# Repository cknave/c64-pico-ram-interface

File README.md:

# Commodore 64 to Raspberry Pi Pico RAM interface

This project exposes a 16 KiB window of a Raspberry Pi Pico's RAM to a Commodore 64 via the
expansion port. It includes a hardware design and software for the Pico C++ SDK.

<table style="border-collapse: collapse"><tr>
<td><figure>
<figcaption>PCB image</figcaption></figure></td>
<td><figure>
<figcaption>Demo video</figcaption></figure>
</tr></table>

## The hardware

**[Schematic PDF](./docs/schematic.pdf)**

Schematic, PCB, and project files are in KiCad 6 format.

5V power from the expansion port is used to power the Pico. As suggested in the Pico datasheet,
a Schottky diode allows the Pico to be connected to powered USB at the same time. 

8-bit buffers bring the 5V logic levels on the address and data bus down to 3.3V to protect
the Pico's GPIO pins. This means that when the C64 reads from the Pico, it's putting a 3.3V
signal on the data bus.  At TTL logic levels, this should be fine.

A switch allows you to toggle between an 8K ROM and a 16K ROM by pulling the /GAME line low.
This loses half the address space, but lets you boot into BASIC.

The tolerances on the PCB design are compatible with [JLCPCB](https://jlcpcb.com/). I ordered
my prototypes from them with ENIG surface finish and gold fingers on a 1.6mm thick board.  You
can get them made much cheaper with HASL, but it will eventually scrape off as you reinsert
the board.

## The firmware

Given a 16 KiB-aligned base address on the Pico's address space, four PIO state machines and
two DMA channels handle reading addresses from the C64 address bus and writing the requested
data to the C64 data bus. The CPU is not needed once this is configured.

To allow the C64 to communicate with the Pico, a 256 byte **command area** is reserved that
will put that byte onto the RX FIFO for the CPU to consume.  The CPU can put any value onto
the TX FIFO to signal that it is ready for more commands.

Between the GPIO pins and the RAM, there are five logical components:

- **address_decoder PIO state machine:** monitors the /ROML and /ROMH lines for reads,
  checks if the address is for the special **command area**, and wakes up either the **read**
  or **command** state machines as needed.  Two copies of this state machine run at the same
  time, monitoring /ROML and /ROMH.
- **read PIO state machine:** reads the address lines, sends the address to DMA, and writes
  the returned data to the data bus
- **command PIO state machine:** reads the low 8 bits of the address, and copies it to the
  RX FIFO for the CPU to handle.  It writes the STATUS register back to the data bus, indicating
  if the CPU is busy or not. The CPU can indicate its readiness by writing any value to the TX FIFO.

  The special value `00` will not be sent to the CPU at all, allowing the C64 to poll the status
  register until the Pico is finished processing a command.
- **DMA channel 1**: write the incoming address to the configuration of DMA channel 2, triggering
  a read
- **DMA channel 2**: copy a byte at the requested RAM address to the read PIO state machine

It's a Rube Goldberg machine, but the Pico's PIO controllers and DMA can do this in well under
the time required by the C64's CPU.

## Further improvements

### Could this work as a 16K ROM and IO ports?

Maybe, but this design is already using all the GPIO pins on the Pico.  Even if you replace
the "input enable" pin (you can probably get away without it), you'll also need to monitor
PHI2.  In my experience, the IO lines are glitchy and you need to make sure that you're actually
in the right part of the clock cycle to use them.

You could try using a shift register to free up a bunch of pins, but you'll waste a lot of
PIO clock cycles shifting all the bits through it.  It might be fast enough to only shift a
couple of bits.

### Could I use all 44 KiB of the available address space?

I think you're definitely in shift register territory at this point, and good luck trying to
decode more than a couple of address prefixes in PIO.  If you actually do this, please contact
me because I want to see it!

## Legal

Distribute under the terms of the BSD 3-clause license.

The [KiCad-RP-Pico footprint](https://github.com/ncarandini/KiCad-RP-Pico) is by
Nicolò Carandini.

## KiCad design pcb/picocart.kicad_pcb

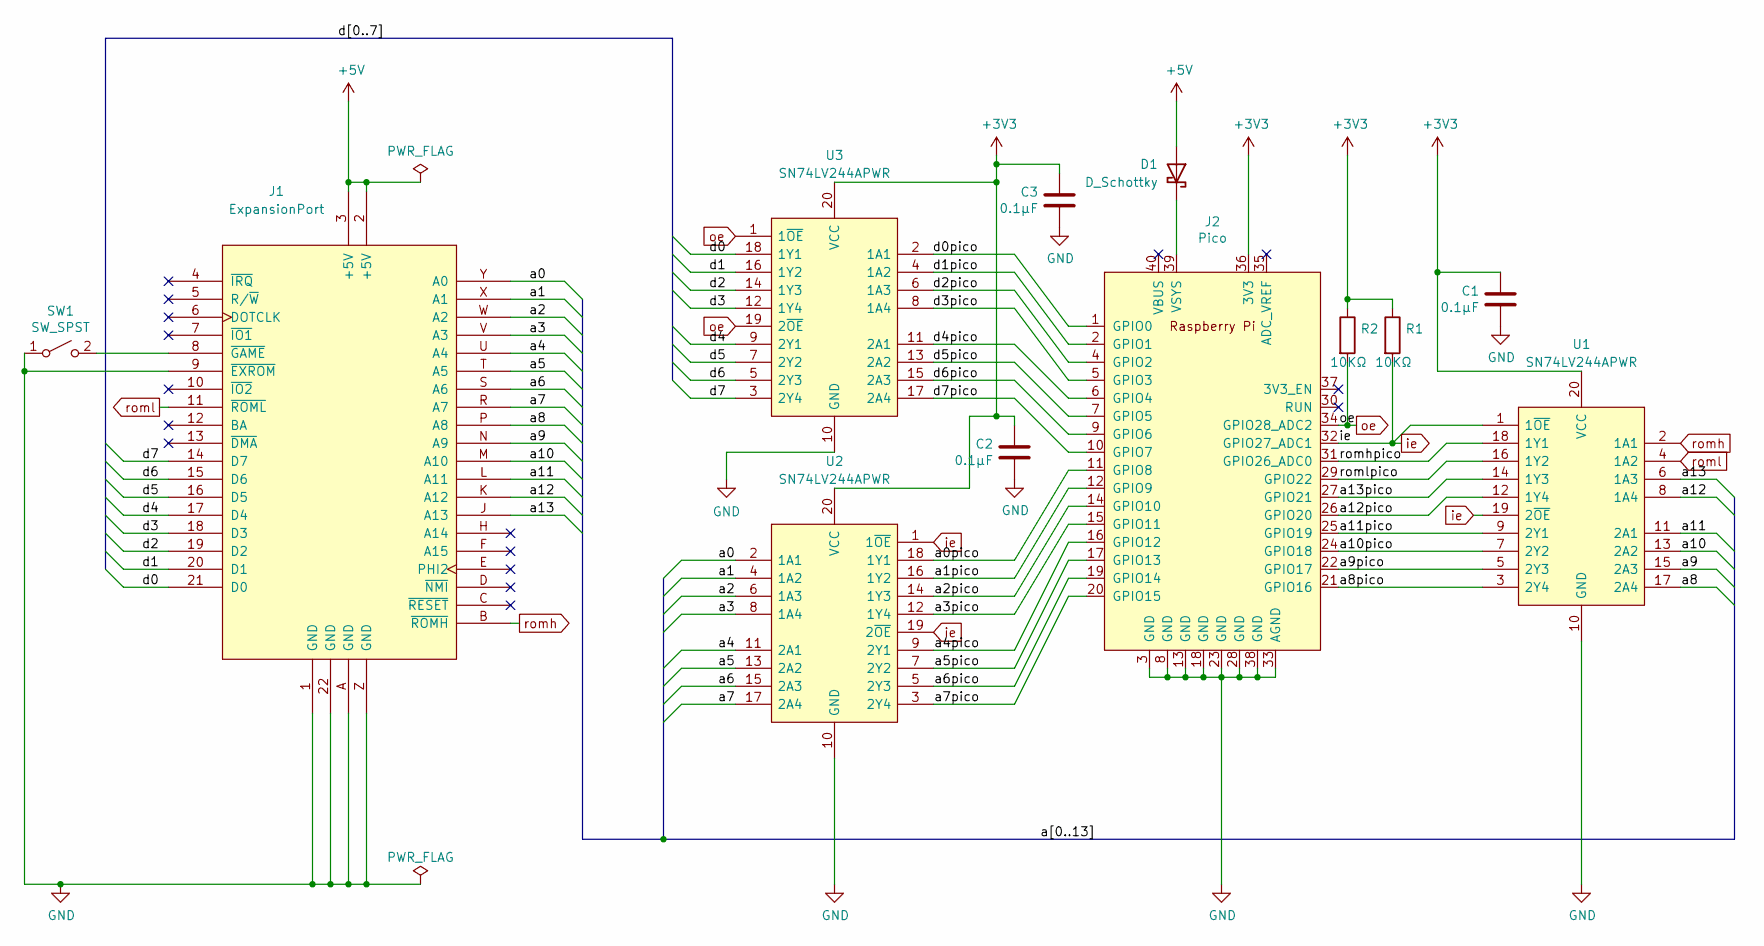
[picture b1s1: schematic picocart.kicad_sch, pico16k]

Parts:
C1, C2, C3: 0.1μF; C_0603_1608Metric_Pad1.08x0.95mm_HandSolder
D1: D_Schottky; D_SMA
J1: ExpansionPort; C64ExpansionEdgeShort
J2: Pico; RPi_Pico_SMD_TH
R1, R2: 10KΩ; R_0603_1608Metric_Pad0.98x0.95mm_HandSolder
SW1: SW_SPST; PinHeader_1x03_P2.54mm_Vertical
U1, U2, U3: SN74LV244APWR; SOP65P640X120-20N; Mouser Part Number 595-SN74LV244APWR

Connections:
+3V3: C1.1, C2.1, C3.1, J2.36 (3V3), R1.1, R2.1, U1.20 (VCC), U2.20 (VCC), U3.20 (VCC)
+5V: D1.2 (A), J1.2 (+5V), J1.3 (+5V)
/a0: J1.Y (A0), U2.2 (1A1)
/a0pico: J2.11 (GPIO8), U2.18 (1Y1)
/a1: J1.X (A1), U2.4 (1A2)
/a1pico: J2.12 (GPIO9), U2.16 (1Y2)
/a2: J1.W (A2), U2.6 (1A3)
/a2pico: J2.14 (GPIO10), U2.14 (1Y3)
/a3: J1.V (A3), U2.8 (1A4)
/a3pico: J2.15 (GPIO11), U2.12 (1Y4)
/a4: J1.U (A4), U2.11 (2A1)
/a4pico: J2.16 (GPIO12), U2.9 (2Y1)
/a5: J1.T (A5), U2.13 (2A2)
/a5pico: J2.17 (GPIO13), U2.7 (2Y2)
/a6: J1.S (A6), U2.15 (2A3)
/a6pico: J2.19 (GPIO14), U2.5 (2Y3)
/a7: J1.R (A7), U2.17 (2A4)
/a7pico: J2.20 (GPIO15), U2.3 (2Y4)
/a8: J1.P (A8), U1.17 (2A4)
/a8pico: J2.21 (GPIO16), U1.3 (2Y4)
/a9: J1.N (A9), U1.15 (2A3)
/a9pico: J2.22 (GPIO17), U1.5 (2Y3)
/a10: J1.M (A10), U1.13 (2A2)
/a10pico: J2.24 (GPIO18), U1.7 (2Y2)
/a11: J1.L (A11), U1.11 (2A1)
/a11pico: J2.25 (GPIO19), U1.9 (2Y1)
/a12: J1.K (A12), U1.8 (1A4)
/a12pico: J2.26 (GPIO20), U1.12 (1Y4)
/a13: J1.J (A13), U1.6 (1A3)
/a13pico: J2.27 (GPIO21), U1.14 (1Y3)
/d0: J1.21 (D0), U3.18 (1Y1)
/d0pico: J2.1 (GPIO0), U3.2 (1A1)
/d1: J1.20 (D1), U3.16 (1Y2)
/d1pico: J2.2 (GPIO1), U3.4 (1A2)
/d2: J1.19 (D2), U3.14 (1Y3)
/d2pico: J2.4 (GPIO2), U3.6 (1A3)
/d3: J1.18 (D3), U3.12 (1Y4)
/d3pico: J2.5 (GPIO3), U3.8 (1A4)
/d4: J1.17 (D4), U3.9 (2Y1)
/d4pico: J2.6 (GPIO4), U3.11 (2A1)
/d5: J1.16 (D5), U3.7 (2Y2)
/d5pico: J2.7 (GPIO5), U3.13 (2A2)
/d6: J1.15 (D6), U3.5 (2Y3)
/d6pico: J2.9 (GPIO6), U3.15 (2A3)
/d7: J1.14 (D7), U3.3 (2Y4)
/d7pico: J2.10 (GPIO7), U3.17 (2A4)
/romhpico: J2.31 (GPIO26_ADC0), U1.18 (1Y1)
/romlpico: J2.29 (GPIO22), U1.16 (1Y2)
GND: C1.2, C2.2, C3.2, J1.1 (GND), J1.9 (~EXROM), J1.22 (GND), J1.A (GND), J1.Z (GND), J2.3 (GND), J2.8 (GND), J2.13 (GND), J2.18 (GND), J2.23 (GND), J2.28 (GND), J2.33 (AGND), J2.38 (GND), SW1.1 (A), U1.10 (GND), U2.10 (GND), U3.10 (GND)
unnamed: D1.1 (K), J2.39 (VSYS)
unnamed: J1.8 (~GAME), SW1.2 (B)
ie: J2.32 (GPIO27_ADC1), R1.2, U1.1 (1~OE), U1.19 (2~OE), U2.1 (1~OE), U2.19 (2~OE)
oe: J2.34 (GPIO28_ADC2), R2.2, U3.1 (1~OE), U3.19 (2~OE)
romh: J1.B (~ROMH), U1.2 (1A1)
roml: J1.11 (~ROML), U1.4 (1A2)

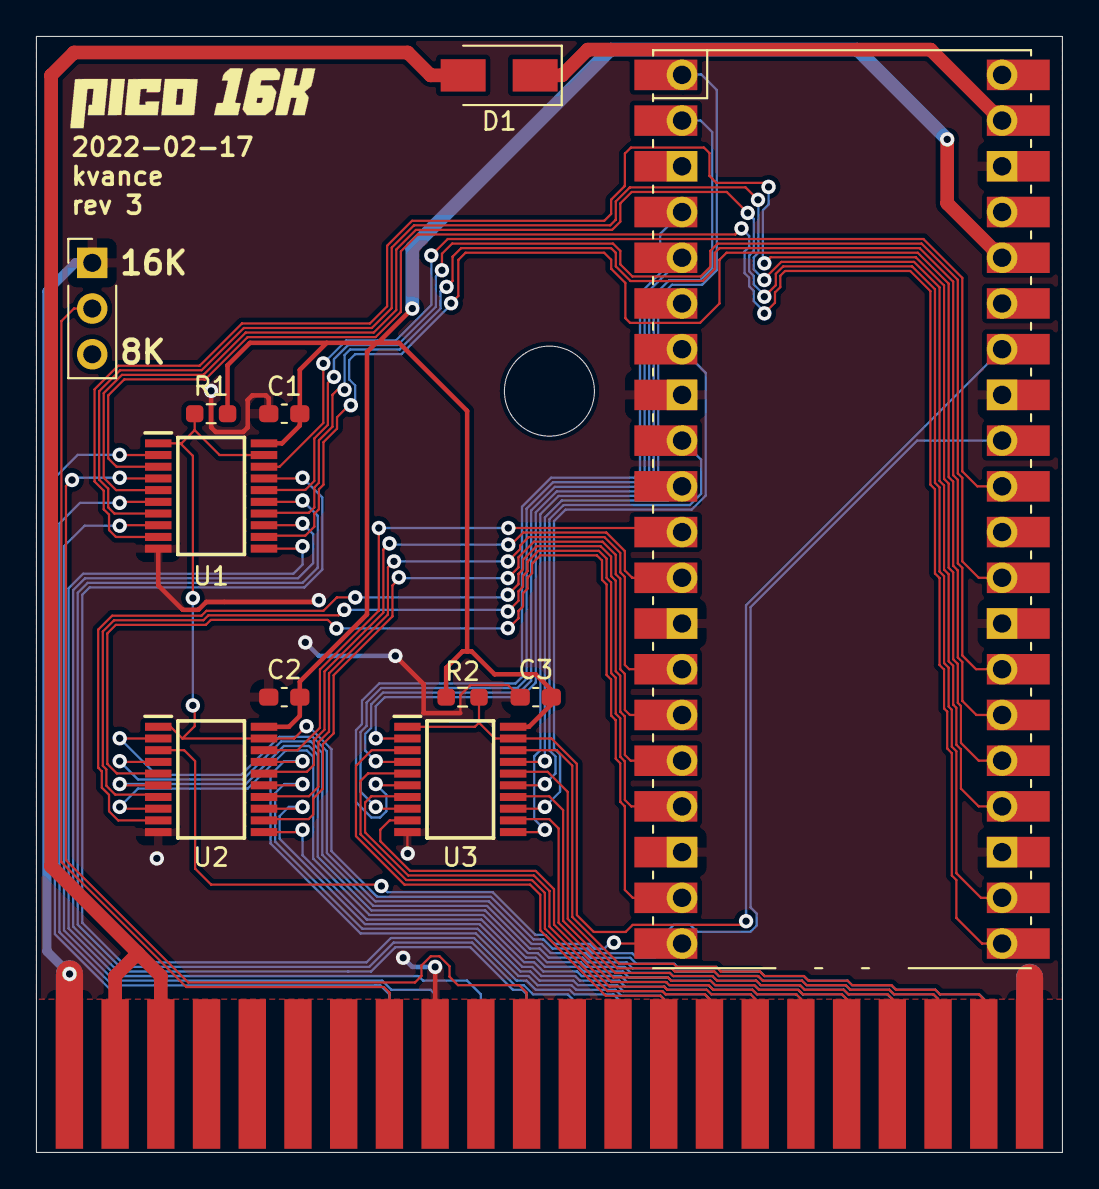
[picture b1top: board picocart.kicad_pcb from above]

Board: 2 copper layers, 57.0 x 62.0 mm, 13 parts (0 on the bottom side), 55 nets.

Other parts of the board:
Ref**: Val**; logo

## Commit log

2022-03-11 Add project code
2022-03-11 Add license
2022-03-11 GitHub does not like when you try to style images
2022-03-12 README: count better
2022-07-16 Pico-W support
2022-07-17 Perform wi-fi scan
    (IRQ handling for blinking the LED is disabled as it seems to conflict
    with the wireless stuff)
2022-07-20 Refactor exposed RAM area
2022-07-21 Can connect to wi-fi (no IP info exposed yet)
